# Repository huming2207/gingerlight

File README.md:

# GingerLight

Yet another CN5816-based LED boost driver board design for 36v 40w COB LED, like CREE CXB2540/3040/3540.

## Usage

- Provide a 20v, 2A DC input (e.g. from a USB PD charger)
- Hook up a 36v 40w LED, like CREE CXB2540/3040/3540 (I've tested with CREE CXB2540 for now), remember to put on a heatsink or otherwise it may become a bit smoky!
- It should work now

## Fine adjustments

- According to CN5816's official datasheet and component calculator:
- When `Vin` = **20v**, `Vled` = **36v**, `Iout` = **0.8A**:
  - 
  - If Vled goes too high, try reducing R1 to 4260kohm
- If you don't want it to be that bright, or you can't afford a big heatsink, then try increasing `R6` (the `Rsw`) to something like 0.2ohm.

## Caveats

According to Consonance FAE, when calculating the resistor divider for voltage threshold reference, the `Vout` here means `Vin` + `Vled`:

For example, my `Vin` is 20v, `Vled` (the LED's `Vf`) is 36v, then `Vout` needs to be 56v, not 36v.

## License 

CC-BY-NC-SA 4.0

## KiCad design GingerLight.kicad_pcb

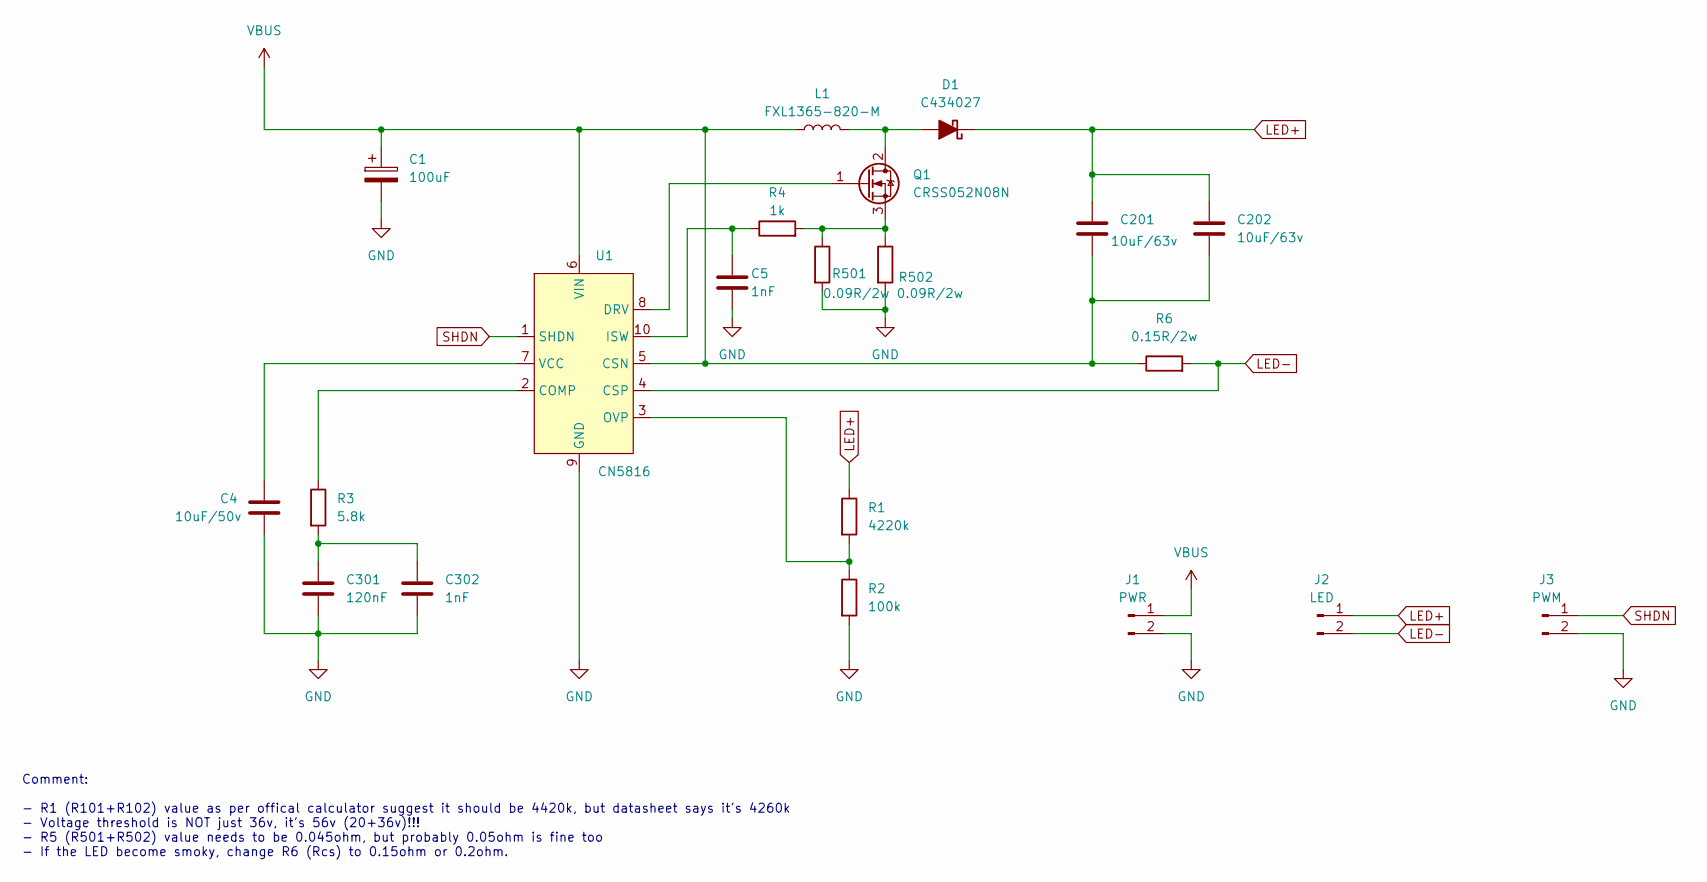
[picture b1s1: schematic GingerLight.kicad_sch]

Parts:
C1: 100uF; CP_Elec_8x10
C4: 10uF/50v; C_1206_3216Metric_Pad1.33x1.80mm_HandSolder
C5, C302: 1nF; C_0603_1608Metric_Pad1.08x0.95mm_HandSolder
C201, C202: 10uF/63v; C_1210_3225Metric_Pad1.33x2.70mm_HandSolder
C301: 120nF; C_0603_1608Metric_Pad1.08x0.95mm_HandSolder
D1: C434027; D_SMA
J1: PWR; PinHeader_1x02_P2.54mm_Vertical
J2: LED; PinHeader_1x02_P2.54mm_Vertical
J3: PWM; PinHeader_1x02_P2.54mm_Vertical
L1: FXL1365-820-M; L_TaiTech_TMPC1265_13.5x12.5mm
Q1: CRSS052N08N; TO-263-2
R1: 4220k; R_0603_1608Metric_Pad0.98x0.95mm_HandSolder
R2: 100k; R_0603_1608Metric_Pad0.98x0.95mm_HandSolder
R3: 5.8k; R_0603_1608Metric_Pad0.98x0.95mm_HandSolder
R4: 1k; R_0603_1608Metric_Pad0.98x0.95mm_HandSolder
R6: 0.15R/2w; R_2512_6332Metric_Pad1.40x3.35mm_HandSolder
R501, R502: 0.09R/2w; R_2512_6332Metric_Pad1.40x3.35mm_HandSolder
U1: CN5816; SSOP-10_3.9x4.9mm_P1.00mm

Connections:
GND: C1.2, C4.2, C5.2, C301.2, C302.2, J1.2, J3.2, R2.2, R501.2, R502.2, U1.9 (GND)
LED+: C201.1, C202.1, D1.1 (K), J2.1, R1.1
LED-: J2.2, R6.2, U1.4 (CSP)
unnamed: C301.1, C302.1, R3.2
unnamed: D1.2 (A), L1.2, Q1.2 (D)
unnamed: Q1.1 (G), U1.8 (DRV)
unnamed: Q1.3 (S), R4.2, R501.1, R502.1
unnamed: R3.1, U1.2 (COMP)
unnamed: C5.1, R4.1, U1.10 (ISW)
unnamed: R1.2, R2.1, U1.3 (OVP)
unnamed: C4.1, U1.7 (VCC)
SHDN: J3.1, U1.1 (SHDN)
VBUS: C1.1, C201.2, C202.2, J1.1, L1.1, R6.1, U1.5 (CSN), U1.6 (VIN)

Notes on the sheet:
Comment: - R1 (R101+R102) value as per offical calculator suggest it should be 4420k, but datasheet says it's 4260k - Voltage threshold is NOT just 36v, it's 56v (20+36v)!!! - R5 (R501+R502) value needs to be 0.045ohm, but probably 0.05ohm is fine too - If the LED become smoky, change R6 (Rcs) to 0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

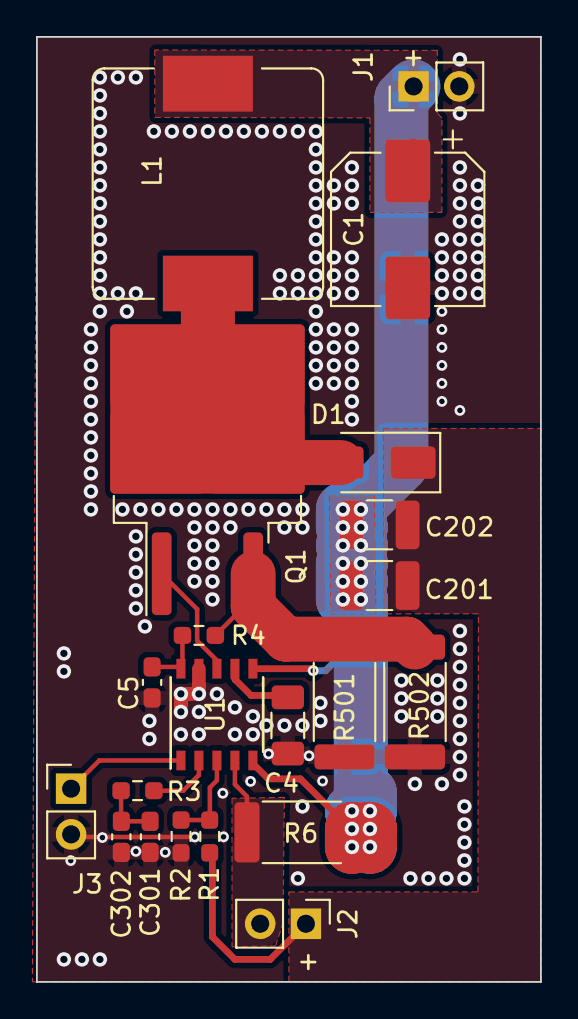
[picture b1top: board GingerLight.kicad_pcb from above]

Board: 2 copper layers, 28.0 x 52.5 mm, 21 parts (0 on the bottom side), 13 nets.

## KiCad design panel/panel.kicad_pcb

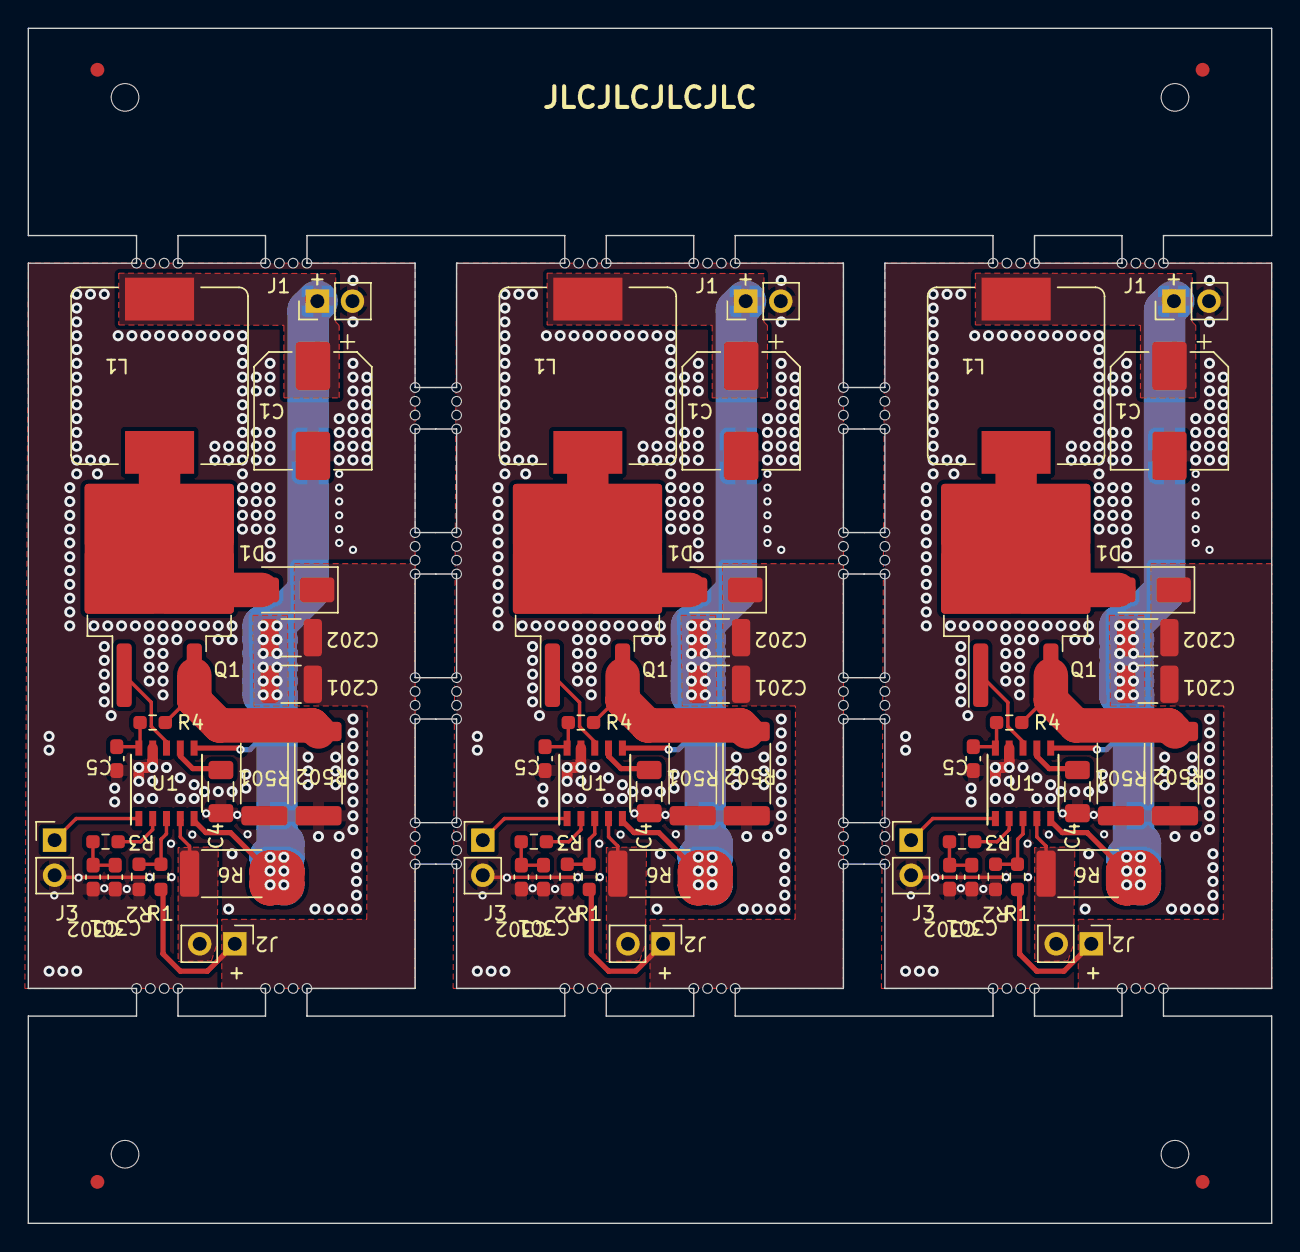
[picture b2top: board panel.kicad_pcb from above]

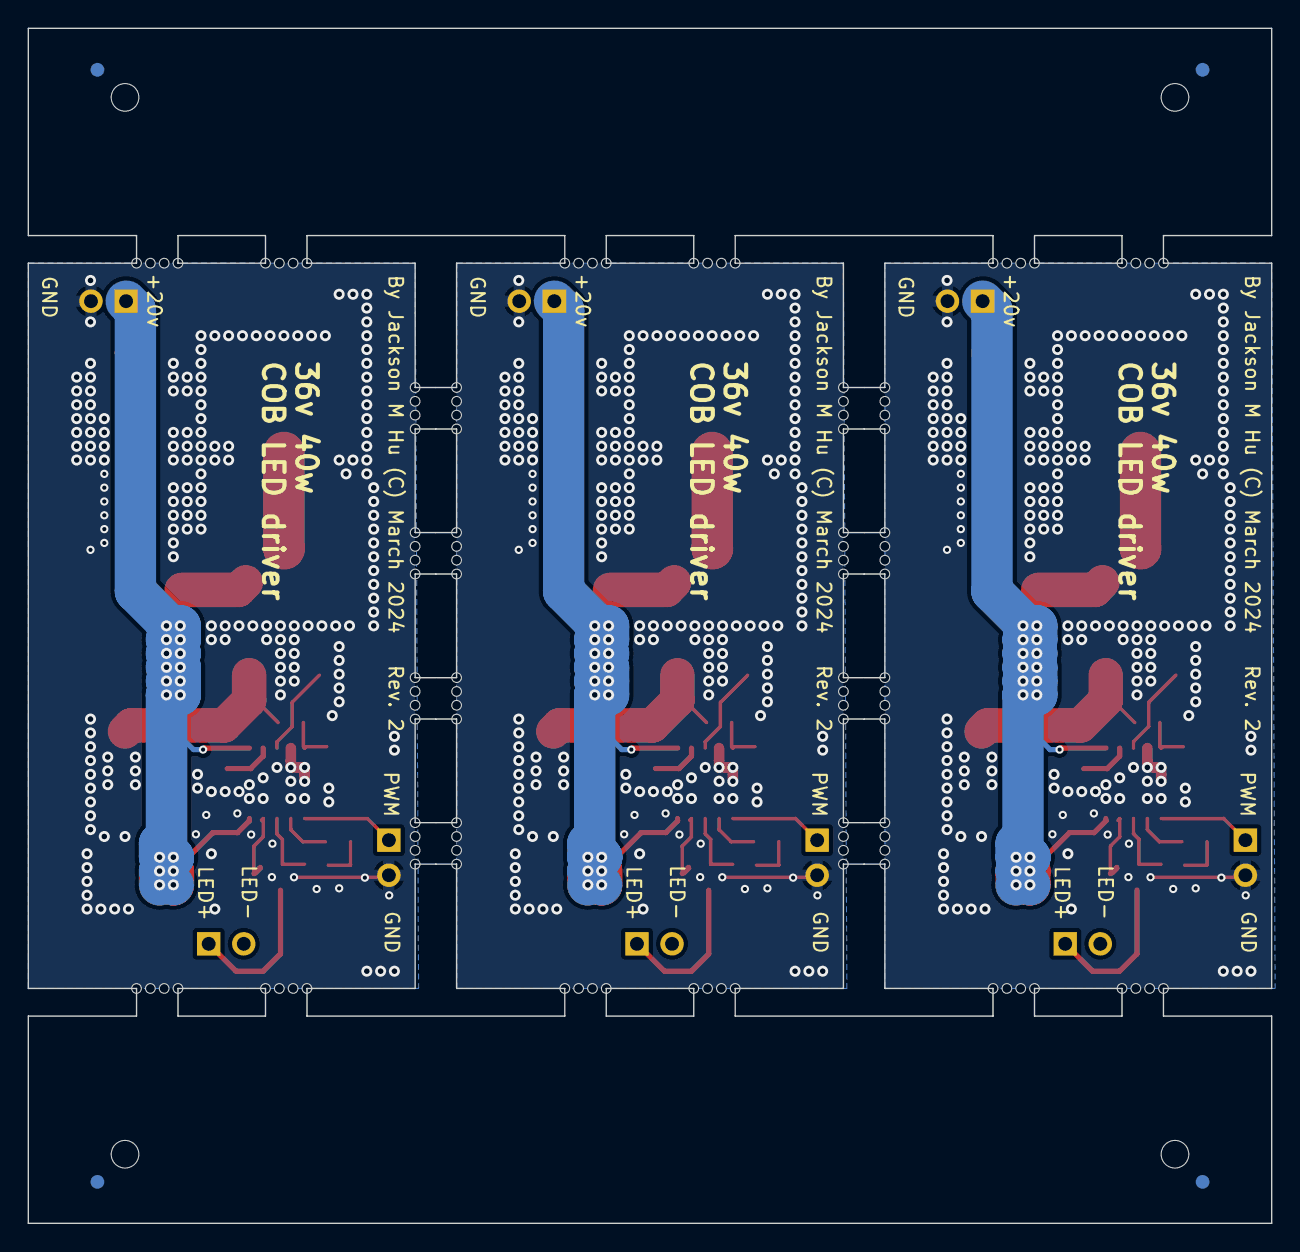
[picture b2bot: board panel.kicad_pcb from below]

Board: 2 copper layers, 90.0 x 86.5 mm, 187 parts (4 on the bottom side), 39 nets.

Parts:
C1, C1#2, C1#3: 100uF; CP_Elec_8x10
C4, C4#2, C4#3: 10uF/50v; C_1206_3216Metric_Pad1.33x1.80mm_HandSolder
C5, C5#2, C5#3, C302, C302#2, C302#3: 1nF; C_0603_1608Metric_Pad1.08x0.95mm_HandSolder
C201, C201#2, C201#3, C202, C202#2, C202#3: 10uF/63v; C_1210_3225Metric_Pad1.33x2.70mm_HandSolder
C301, C301#2, C301#3: 120nF; C_0603_1608Metric_Pad1.08x0.95mm_HandSolder
D1, D1#2, D1#3: C434027; D_SMA
J1, J1#2, J1#3: PWR; PinHeader_1x02_P2.54mm_Vertical
J2, J2#2, J2#3: LED; PinHeader_1x02_P2.54mm_Vertical
J3, J3#2, J3#3: PWM; PinHeader_1x02_P2.54mm_Vertical
KiKit_FID_B_1, KiKit_FID_B_2, KiKit_FID_B_3, KiKit_FID_B_4: Fiducial
KiKit_FID_T_1, KiKit_FID_T_2, KiKit_FID_T_3, KiKit_FID_T_4: Fiducial
KiKit_MB_1_1, KiKit_MB_1_2, KiKit_MB_1_3, KiKit_MB_1_4, KiKit_MB_2_1, KiKit_MB_2_2, KiKit_MB_2_3, KiKit_MB_2_4, KiKit_MB_3_1, KiKit_MB_3_2, KiKit_MB_3_3, KiKit_MB_3_4, KiKit_MB_4_1, KiKit_MB_4_2, KiKit_MB_4_3, KiKit_MB_4_4, KiKit_MB_5_1, KiKit_MB_5_2, KiKit_MB_5_3, KiKit_MB_5_4, KiKit_MB_6_1, KiKit_MB_6_2, KiKit_MB_6_3, KiKit_MB_6_4, KiKit_MB_7_1, KiKit_MB_7_2, KiKit_MB_7_3, KiKit_MB_7_4, KiKit_MB_8_1, KiKit_MB_8_2, KiKit_MB_8_3, KiKit_MB_8_4, KiKit_MB_9_1, KiKit_MB_9_2, KiKit_MB_9_3, KiKit_MB_9_4, KiKit_MB_10_1, KiKit_MB_10_2, KiKit_MB_10_3, KiKit_MB_10_4, KiKit_MB_11_1, KiKit_MB_11_2, KiKit_MB_11_3, KiKit_MB_11_4, KiKit_MB_12_1, KiKit_MB_12_2, KiKit_MB_12_3, KiKit_MB_12_4, KiKit_MB_13_1, KiKit_MB_13_2, KiKit_MB_13_3, KiKit_MB_13_4, KiKit_MB_14_1, KiKit_MB_14_2, KiKit_MB_14_3, KiKit_MB_14_4, KiKit_MB_15_1, KiKit_MB_15_2, KiKit_MB_15_3, KiKit_MB_15_4, KiKit_MB_16_1, KiKit_MB_16_2, KiKit_MB_16_3, KiKit_MB_16_4, KiKit_MB_17_1, KiKit_MB_17_2, KiKit_MB_17_3, KiKit_MB_17_4, KiKit_MB_18_1, KiKit_MB_18_2, KiKit_MB_18_3, KiKit_MB_18_4, KiKit_MB_19_1, KiKit_MB_19_2, KiKit_MB_19_3, KiKit_MB_19_4, KiKit_MB_20_1, KiKit_MB_20_2, KiKit_MB_20_3, KiKit_MB_20_4, KiKit_MB_21_1, KiKit_MB_21_2, KiKit_MB_21_3, KiKit_MB_21_4, KiKit_MB_22_1, KiKit_MB_22_2, KiKit_MB_22_3, KiKit_MB_22_4, KiKit_MB_23_1, KiKit_MB_23_2, KiKit_MB_23_3, KiKit_MB_23_4, KiKit_MB_24_1, KiKit_MB_24_2, KiKit_MB_24_3, KiKit_MB_24_4, KiKit_MB_25_1, KiKit_MB_25_2, KiKit_MB_25_3, KiKit_MB_25_4, KiKit_MB_26_1, KiKit_MB_26_2, KiKit_MB_26_3, KiKit_MB_26_4, KiKit_MB_27_1, KiKit_MB_27_2, KiKit_MB_27_3, KiKit_MB_27_4, KiKit_MB_28_1, KiKit_MB_28_2, KiKit_MB_28_3, KiKit_MB_28_4: NPTH
KiKit_TO_1, KiKit_TO_2, KiKit_TO_3, KiKit_TO_4: NPTH
L1, L1#2, L1#3: FXL1365-820-M; L_TaiTech_TMPC1265_13.5x12.5mm
Q1, Q1#2, Q1#3: CRSS052N08N; TO-263-2
R1, R1#2, R1#3: 4220k; R_0603_1608Metric_Pad0.98x0.95mm_HandSolder
R2, R2#2, R2#3: 100k; R_0603_1608Metric_Pad0.98x0.95mm_HandSolder
R3, R3#2, R3#3: 5.8k; R_0603_1608Metric_Pad0.98x0.95mm_HandSolder
R4, R4#2, R4#3: 1k; R_0603_1608Metric_Pad0.98x0.95mm_HandSolder
R6, R6#2, R6#3: 0.15R/2w; R_2512_6332Metric_Pad1.40x3.35mm_HandSolder
R501, R501#2, R501#3, R502, R502#2, R502#3: 0.09R/2w; R_2512_6332Metric_Pad1.40x3.35mm_HandSolder
U1, U1#2, U1#3: CN5816; SSOP-10_3.9x4.9mm_P1.00mm

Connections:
Board_0-GND: C1#3.2, C4.2, C5#3.2, C301#3.2, C302#3.2, J1.2, J3#2.2, R2#3.2, R501#2.2, R502#3.2, U1#2.9 (GND)
Board_0-LED+: C201.1, C202#3.1, D1#2.1 (K), J2#3.1, R1#2.1
Board_0-LED-: J2#3.2, R6#3.2, U1#2.4 (CSP)
Board_0-Net-(C301-Pad1): C301#3.1, C302#3.1, R3#3.2
Board_0-Net-(D1-A): D1#2.2 (A), L1#3.2, Q1#3.2 (D)
Board_0-Net-(Q1-G): Q1#3.1 (G), U1#2.8 (DRV)
Board_0-Net-(Q1-S): Q1#3.3 (S), R4#3.2, R501#2.1, R502#3.1
Board_0-Net-(U1-COMP): R3#3.1, U1#2.2 (COMP)
Board_0-Net-(U1-ISW): C5#3.1, R4#3.1, U1#2.10 (ISW)
Board_0-Net-(U1-OVP): R1#2.2, R2#3.1, U1#2.3 (OVP)
Board_0-Net-(U1-VCC): C4.1, U1#2.7 (VCC)
Board_0-SHDN: J3#2.1, U1#2.1 (SHDN)
Board_0-VBUS: C1#3.1, C201.2, C202#3.2, J1.1, L1#3.1, R6#3.1, U1#2.5 (CSN), U1#2.6 (VIN)
Board_1-GND: C1.2, C4#3.2, C5.2, C301.2, C302.2, J1#3.2, J3#3.2, R2.2, R501.2, R502.2, U1.9 (GND)
Board_1-LED+: C201#3.1, C202.1, D1#3.1 (K), J2#2.1, R1#3.1
Board_1-LED-: J2#2.2, R6.2, U1.4 (CSP)
Board_1-Net-(C301-Pad1): C301.1, C302.1, R3.2
Board_1-Net-(D1-A): D1#3.2 (A), L1#2.2, Q1.2 (D)
Board_1-Net-(Q1-G): Q1.1 (G), U1.8 (DRV)
Board_1-Net-(Q1-S): Q1.3 (S), R4#2.2, R501.1, R502.1
Board_1-Net-(U1-COMP): R3.1, U1.2 (COMP)
Board_1-Net-(U1-ISW): C5.1, R4#2.1, U1.10 (ISW)
Board_1-Net-(U1-OVP): R1#3.2, R2.1, U1.3 (OVP)
Board_1-Net-(U1-VCC): C4#3.1, U1.7 (VCC)
Board_1-SHDN: J3#3.1, U1.1 (SHDN)
Board_1-VBUS: C1.1, C201#3.2, C202.2, J1#3.1, L1#2.1, R6.1, U1.5 (CSN), U1.6 (VIN)
Board_2-GND: C1#2.2, C4#2.2, C5#2.2, C301#2.2, C302#2.2, J1#2.2, J3.2, R2#2.2, R501#3.2, R502#2.2, U1#3.9 (GND)
Board_2-LED+: C201#2.1, C202#2.1, D1.1 (K), J2.1, R1.1
Board_2-LED-: J2.2, R6#2.2, U1#3.4 (CSP)
Board_2-Net-(C301-Pad1): C301#2.1, C302#2.1, R3#2.2
Board_2-Net-(D1-A): D1.2 (A), L1.2, Q1#2.2 (D)
Board_2-Net-(Q1-G): Q1#2.1 (G), U1#3.8 (DRV)
Board_2-Net-(Q1-S): Q1#2.3 (S), R4.2, R501#3.1, R502#2.1
Board_2-Net-(U1-COMP): R3#2.1, U1#3.2 (COMP)
Board_2-Net-(U1-ISW): C5#2.1, R4.1, U1#3.10 (ISW)
Board_2-Net-(U1-OVP): R1.2, R2#2.1, U1#3.3 (OVP)
Board_2-Net-(U1-VCC): C4#2.1, U1#3.7 (VCC)
Board_2-SHDN: J3.1, U1#3.1 (SHDN)
Board_2-VBUS: C1#2.1, C201#2.2, C202#2.2, J1#2.1, L1.1, R6#2.1, U1#3.5 (CSN), U1#3.6 (VIN)

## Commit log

2024-02-14 Init
2024-02-15 Rev 1
2024-02-16 Rev 1.1
2024-02-16 Add README
2024-02-29 Rev 2
2024-02-29 Rev 2: add panel & gerber
